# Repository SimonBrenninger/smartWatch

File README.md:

# smartWatch

is a simple, digital wristwatch that uses LEDs to indicate the position of each clock arm.

## Smart Features

The smartWatch incorporates an nRF52810 for handling BLE connectivity to send the monitored data regularly to the host device.

## PCB Design

The PCB was designed using [KiCad](https://kicad.org).

PCB front-side

PCB back-side

## Future Features

A future revision will include a biomedical sensor to enable even more smart functionalities i.e. SpO2 and heart-rate measurements.

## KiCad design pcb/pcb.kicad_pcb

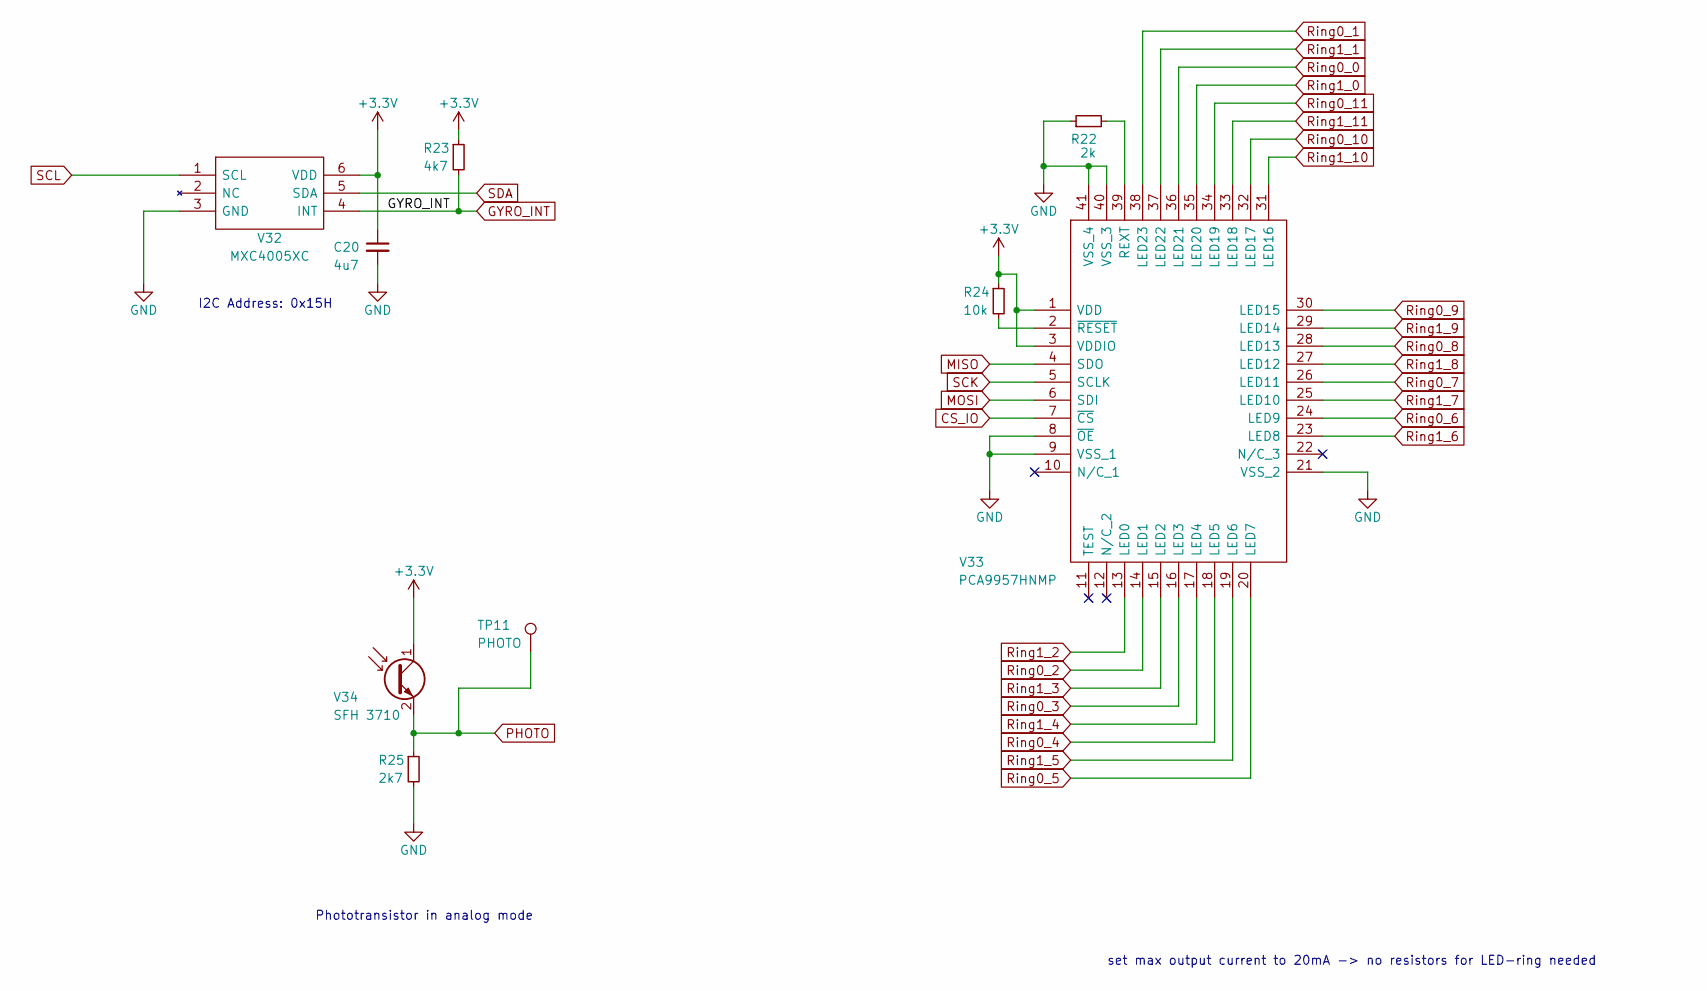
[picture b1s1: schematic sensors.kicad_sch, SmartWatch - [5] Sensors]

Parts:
C20: 4u7; C_0603_1608Metric
R22: 2k; R_0603_1608Metric
R23: 4k7; R_0603_1608Metric
R24: 10k; R_0603_1608Metric
R25: 2k7; R_0603_1608Metric
TP11: PHOTO; TestPoint_Pad_D1.0mm
V32: MXC4005XC; Mouser Part Number 438-MXC4005XC
V33: PCA9957HNMP; QFN-40-1EP_5x5mm_P0.4mm_EP3.6x3.6mm; Manufacturer_Part_Number PCA9957HNMP; Mouser Part Number PCA9957HNMP
V34: SFH 3710; LEDC2012X95N; Mouser Part Number SFH 3710-Z

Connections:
3.3V: C20.1, R23.1, R24.1, V32.6 (VDD), V33.1 (VDD), V33.3 (VDDIO), V34.1 (C); also elsewhere on the board
BAT_PROT-: C20.2, R22.1, R25.2, V32.3 (GND), V33.8 (~OE), V33.9 (VSS_1), V33.21 (VSS_2), V33.40 (VSS_3), V33.41 (VSS_4); also elsewhere on the board
CS_IO: V33.7 (~CS); also elsewhere on the board
GYRO_INT: R23.2, V32.4 (INT); also elsewhere on the board
MISO: V33.4 (SDO); also elsewhere on the board
MOSI: V33.6 (SDI); also elsewhere on the board
unnamed: R22.2, V33.39 (REXT)
unnamed: R24.2, V33.2 (~RESET)
PHOTO: R25.1, TP11.1, V34.2 (E); also elsewhere on the board
Ring0_0: V33.36 (LED21); also elsewhere on the board
Ring0_1: V33.38 (LED23); also elsewhere on the board
Ring0_2: V33.14 (LED1); also elsewhere on the board
Ring0_3: V33.16 (LED3); also elsewhere on the board
Ring0_4: V33.18 (LED5); also elsewhere on the board
Ring0_5: V33.20 (LED7); also elsewhere on the board
Ring0_6: V33.24 (LED9); also elsewhere on the board
Ring0_7: V33.26 (LED11); also elsewhere on the board
Ring0_8: V33.28 (LED13); also elsewhere on the board
Ring0_9: V33.30 (LED15); also elsewhere on the board
Ring0_10: V33.32 (LED17); also elsewhere on the board
Ring0_11: V33.34 (LED19); also elsewhere on the board
Ring1_0: V33.35 (LED20); also elsewhere on the board
Ring1_1: V33.37 (LED22); also elsewhere on the board
Ring1_2: V33.13 (LED0); also elsewhere on the board
Ring1_3: V33.15 (LED2); also elsewhere on the board
Ring1_4: V33.17 (LED4); also elsewhere on the board
Ring1_5: V33.19 (LED6); also elsewhere on the board
Ring1_6: V33.23 (LED8); also elsewhere on the board
Ring1_7: V33.25 (LED10); also elsewhere on the board
Ring1_8: V33.27 (LED12); also elsewhere on the board
Ring1_9: V33.29 (LED14); also elsewhere on the board
Ring1_10: V33.31 (LED16); also elsewhere on the board
Ring1_11: V33.33 (LED18); also elsewhere on the board
SCK: V33.5 (SCLK); also elsewhere on the board
SCL: V32.1 (SCL); also elsewhere on the board
SDA: V32.5 (SDA); also elsewhere on the board

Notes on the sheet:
set max output current to 20mA -> no resistors for LED-ring needed
I2C Address: 0x15H
Phototransistor in analog mode

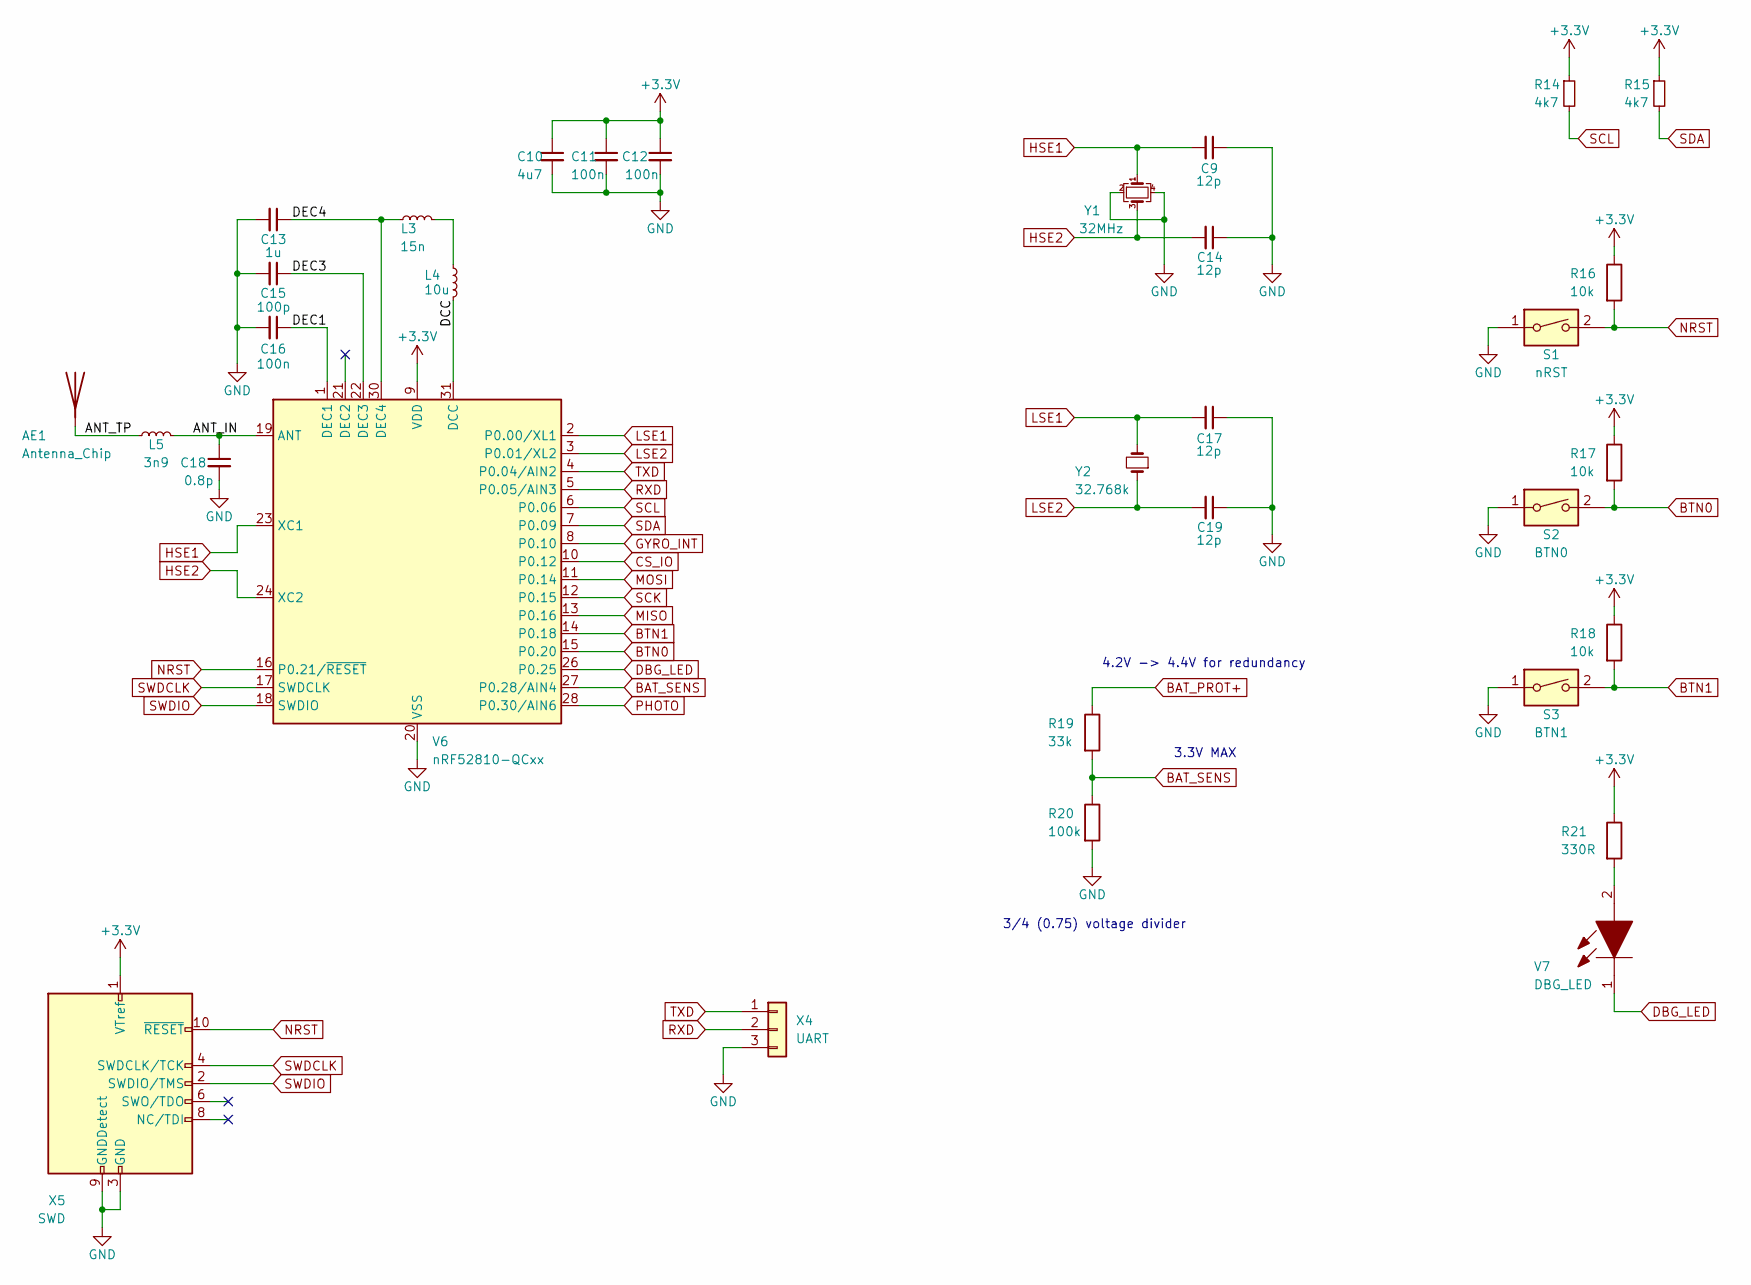
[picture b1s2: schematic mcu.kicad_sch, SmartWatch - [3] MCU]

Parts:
AE1: Antenna_Chip; Ignion_NN01-102_BT_WIFI
C9, C14, C17, C19: 12p; C_0603_1608Metric
C10: 4u7; C_0603_1608Metric
C11, C12, C16: 100n; C_0603_1608Metric
C13: 1u; C_0603_1608Metric
C15: 100p; C_0603_1608Metric
C18: 0.8p; C_0603_1608Metric
L3: 15n; L_0603_1608Metric
L4: 10u; L_0603_1608Metric
L5: 3n9; L_0603_1608Metric
R14, R15: 4k7; R_0603_1608Metric
R16, R17, R18: 10k; R_0603_1608Metric
R19: 33k; R_0603_1608Metric
R20: 100k; R_0603_1608Metric
R21: 330R; R_0603_1608Metric
S1: nRST; SW_SPST_EVQP2
S2: BTN0; Tactile_Panasonic_EVQP7J01P
S3: BTN1; Tactile_Panasonic_EVQP7J01P
V6: nRF52810-QCxx; QFN-32-1EP_5x5mm_P0.5mm_EP3.6x3.6mm
V7: DBG_LED; LEDC1608X80N; Mouser Part Number 710-150060SS75000
X4: UART; PinHeader_2x03_P1.27mm_Vertical_SMD
X5: SWD; PinHeader_2x05_P1.27mm_Vertical_SMD
Y1: 32MHz; Crystal_SMD_2520-4Pin_2.5x2.0mm; Mouser Part Number ECS-320-8-36CKM-TR3
Y2: 32.768k; Crystal_SMD_3215-2Pin_3.2x1.5mm; Mouser Part Number ECS-.327-9-34B-C-TR

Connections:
3.3V: C10.1, C11.1, C12.1, R14.1, R15.1, R16.1, R17.1, R18.1, R21.1, V6.9 (VDD), V6.25 (VDD), V6.32 (VDD), X5.1 (VTref); also elsewhere on the board
/MCU/ANT_IN: C18.1, L5.2, V6.19 (ANT)
/MCU/ANT_TP: AE1.1 (A), L5.1
/MCU/DCC: L4.1, V6.31 (DCC)
/MCU/DEC1: C16.1, V6.1 (DEC1)
/MCU/DEC3: C15.1, V6.22 (DEC3)
/MCU/DEC4: C13.1, L3.2, V6.30 (DEC4)
BAT_PROT+: R19.1; also elsewhere on the board
BAT_PROT-: C9.1, C10.2, C11.2, C12.2, C13.2, C14.1, C15.2, C16.2, C17.1, C18.2, C19.1, R20.2, S1.1, S2.1, S3.1, V6.20 (VSS), V6.29 (VSS), V6.33 (VSS), X4.3, X5.3 (GND), X5.5 (GND), X5.9 (GNDDetect), Y1.2, Y1.4; also elsewhere on the board
BAT_SENS: R19.2, R20.1, V6.27 (P0.28/AIN4)
BTN0: R17.2, S2.2, V6.15 (P0.20)
BTN1: R18.2, S3.2, V6.14 (P0.18)
CS_IO: V6.10 (P0.12); also elsewhere on the board
DBG_LED: V6.26 (P0.25), V7.1
GYRO_INT: V6.8 (P0.10); also elsewhere on the board
HSE1: C9.2, V6.23 (XC1), Y1.1
HSE2: C14.2, V6.24 (XC2), Y1.3
LSE1: C17.2, V6.2 (P0.00/XL1), Y2.2
LSE2: C19.2, V6.3 (P0.01/XL2), Y2.1
MISO: V6.13 (P0.16); also elsewhere on the board
MOSI: V6.11 (P0.14); also elsewhere on the board
NRST: R16.2, S1.2, V6.16 (P0.21/~RESET), X5.10 (~RESET)
unnamed: L3.1, L4.2
unnamed: R21.2, V7.2
PHOTO: V6.28 (P0.30/AIN6); also elsewhere on the board
RXD: V6.5 (P0.05/AIN3), X4.2
SCK: V6.12 (P0.15); also elsewhere on the board
SCL: R14.2, V6.6 (P0.06); also elsewhere on the board
SDA: R15.2, V6.7 (P0.09); also elsewhere on the board
SWDCLK: V6.17 (SWDCLK), X5.4 (SWDCLK/TCK)
SWDIO: V6.18 (SWDIO), X5.2 (SWDIO/TMS)
TXD: V6.4 (P0.04/AIN2), X4.1

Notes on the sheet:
4.2V -> 4.4V for redundancy
3/4 (0.75) voltage divider
3.3V MAX

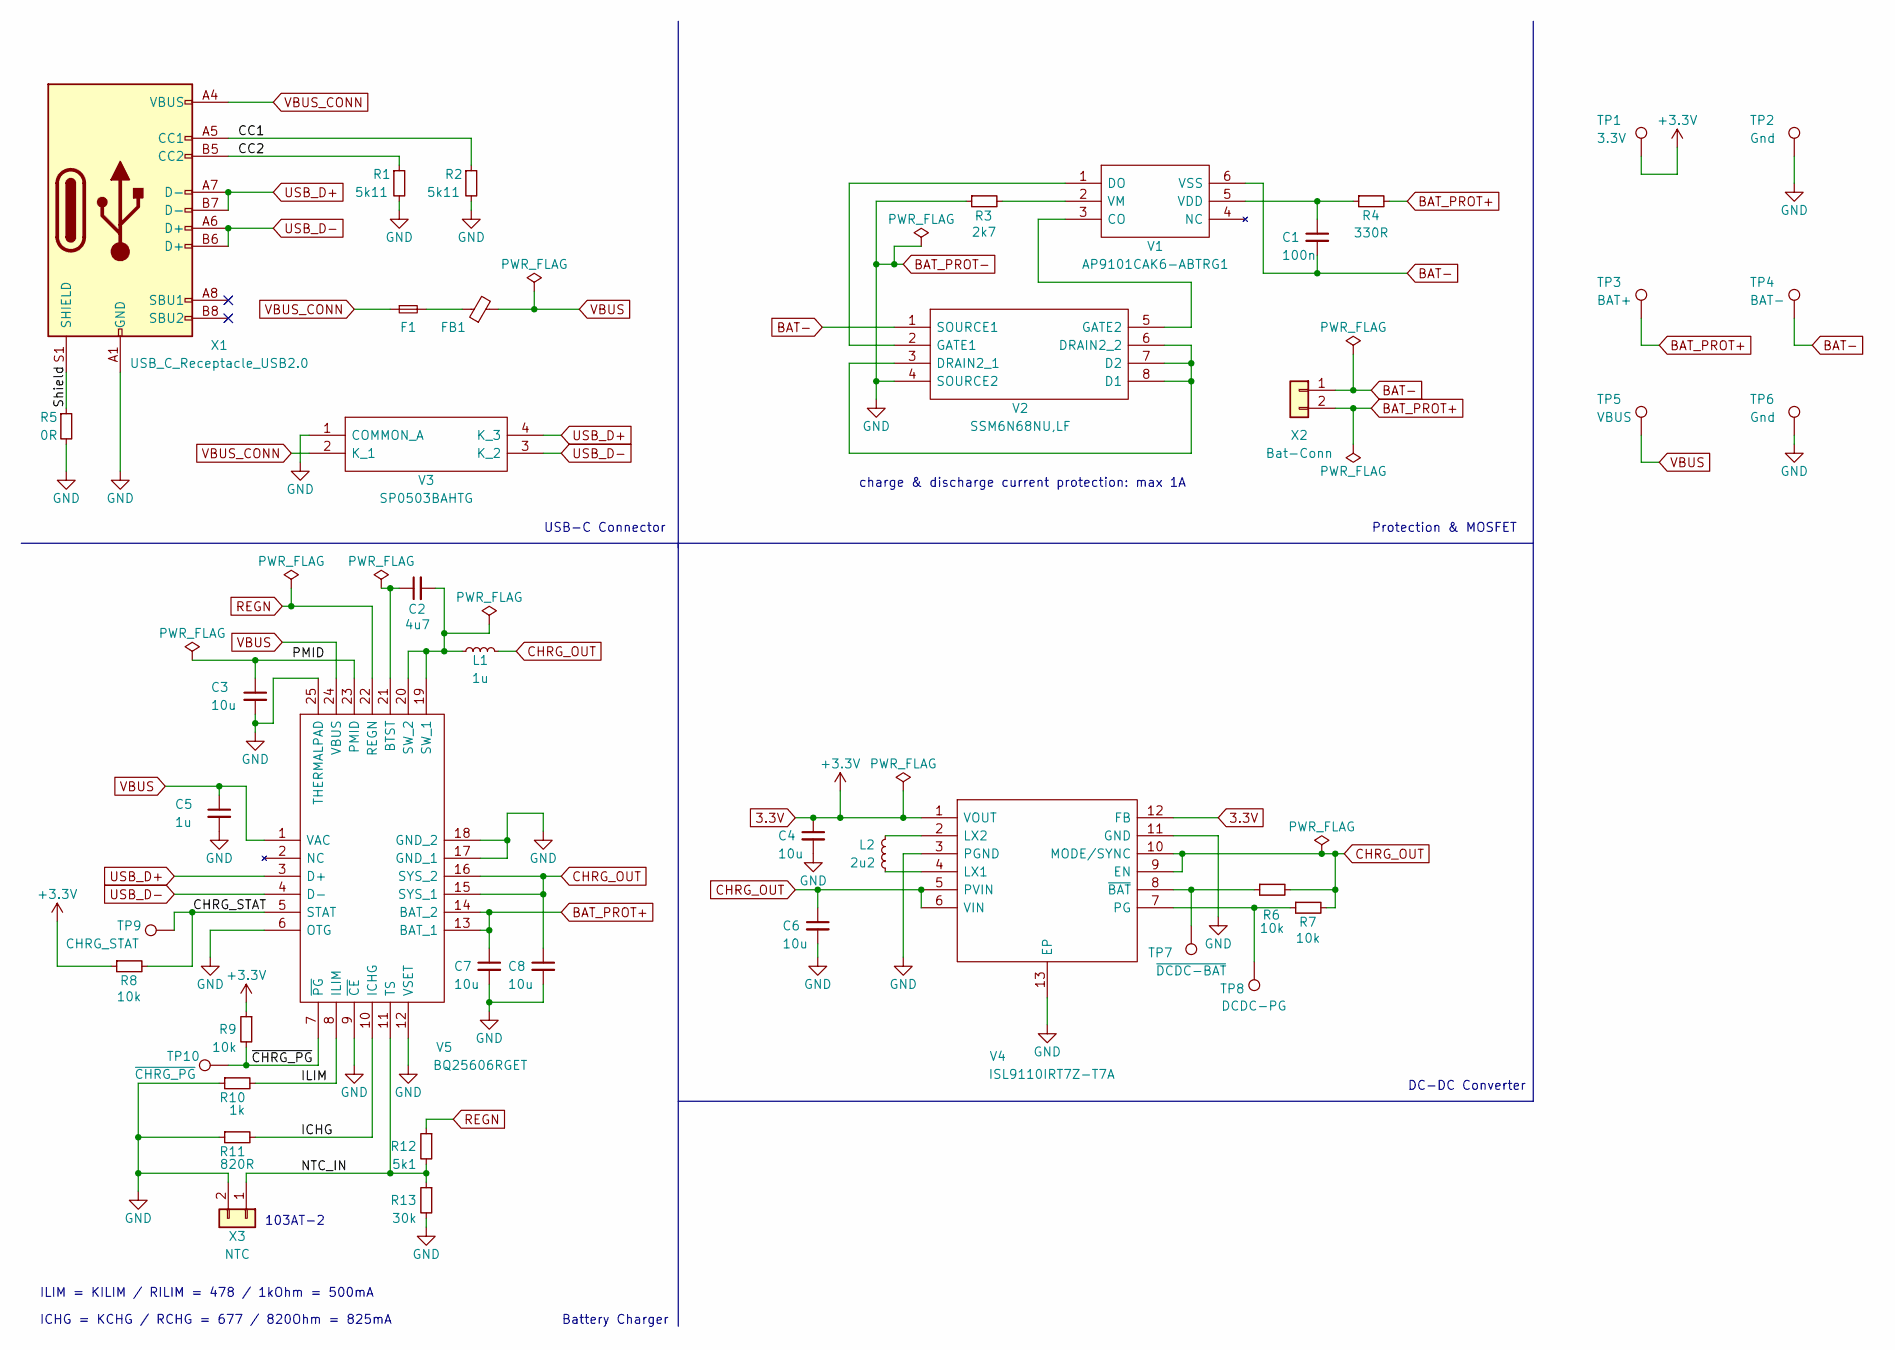
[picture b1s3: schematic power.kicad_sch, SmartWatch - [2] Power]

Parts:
C1: 100n; C_0603_1608Metric
C2: 4u7; C_0603_1608Metric
C3, C4, C6, C7, C8: 10u; C_0603_1608Metric
C5: 1u; C_0603_1608Metric
F1: Fuse_1A; Fuse_0603_1608Metric_Pad1.05x0.95mm_HandSolder
FB1: FerriteBead_Small; L_0805_2012Metric
L1: 1u; L_0603_1608Metric
L2: 2u2; L_1008_2520Metric
R1, R2: 5k11; R_0603_1608Metric
R3: 2k7; R_0603_1608Metric
R4: 330R; R_2512_6332Metric
R5: 0R; R_0603_1608Metric
R6, R7, R8, R9: 10k; R_0603_1608Metric
R10: 1k; R_0603_1608Metric
R11: 820R; R_0603_1608Metric
R12: 5k1; R_0603_1608Metric
R13: 30k; R_0603_1608Metric
TP1: 3.3V; TestPoint_Pad_D1.0mm
TP2, TP6: Gnd; TestPoint_Pad_D1.0mm
TP3: BAT+; TestPoint_Pad_D1.0mm
TP4: BAT-; TestPoint_Pad_D1.0mm
TP5: VBUS; TestPoint_Pad_D1.0mm
TP7: ~{DCDC-BAT}; TestPoint_Pad_D1.0mm
TP8: DCDC-PG; TestPoint_Pad_D1.0mm
TP9: CHRG_STAT; TestPoint_Pad_D1.0mm
TP10: ~{CHRG_PG}; TestPoint_Pad_D1.0mm
V1: AP9101CAK6-ABTRG1; SOT95P285X140-6N; Mouser Part Number 621-AP9101CAK6ABTRG1
V2: SSM6N68NU,LF; SSM6N68NULF; Manufacturer_Part_Number SSM6N68NU,LF; Mouser Part Number 757-SSM6N68NULF
V3: SP0503BAHTG; Manufacturer_Part_Number SP0503BAHTG; Mouser Part Number 576-SP0503BAHTG
V4: ISL9110IRT7Z-T7A; SON40P300X300X75-13N; Mouser Part Number 968-ISL9110IRT7Z-T7A
V5: BQ25606RGET; QFN50P400X400X100-25N; Mouser2 Part Number 595-BQ25606RGET
X1: USB_C_Receptacle_USB2.0; USB_C_Receptacle_Amphenol_12401598; Mouser Part Number 12401598E4#2A
X2: Bat-Conn; JST_PH_B2B-PH-SM4-TB_1x02-1MP_P2.00mm_Vertical
X3: NTC; PinHeader_P2mm_1x02_SMD

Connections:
3.3V: C4.1, R8.1, R9.1, TP1.1, V4.1 (VOUT), V4.12 (FB); also elsewhere on the board
/Power/CC1: R2.1, X1.A5 (CC1)
/Power/CC2: R1.1, X1.B5 (CC2)
/Power/CHRG_STAT: R8.2, TP9.1, V5.5 (STAT)
/Power/ICHG: R11.2, V5.10 (ICHG)
/Power/ILIM: R10.2, V5.8 (ILIM)
/Power/NTC_IN: R12.2, R13.1, V5.11 (TS), X3.1
/Power/PMID: C3.1, V5.23 (PMID)
/Power/Shield: R5.1, X1.S1 (SHIELD)
/Power/~CHRG_PG: R9.2, TP10.1, V5.7 (~PG)
BAT-: C1.2, TP4.1, V1.6 (VSS), V2.1 (SOURCE1), X2.1
BAT_PROT+: C7.1, R4.2, TP3.1, V5.13 (BAT_1), V5.14 (BAT_2), X2.2; also elsewhere on the board
BAT_PROT-: C3.2, C4.2, C5.2, C6.2, C7.2, C8.2, R1.2, R2.2, R3.1, R5.2, R10.1, R11.1, R13.2, TP2.1, TP6.1, V2.4 (SOURCE2), V3.1 (COMMON_A), V4.3 (PGND), V4.11 (GND), V4.13 (EP), V5.6 (OTG), V5.9 (~CE), V5.12 (VSET), V5.17 (GND_1), V5.18 (GND_2), V5.25 (THERMALPAD), X1.A1 (GND), X1.A12 (GND), X1.B1 (GND), X1.B12 (GND), X3.2; also elsewhere on the board
CHRG_OUT: C6.1, C8.1, L1.2, R6.2, R7.2, V4.5 (PVIN), V4.6 (VIN), V4.9 (EN), V4.10 (MODE/SYNC), V5.15 (SYS_1), V5.16 (SYS_2)
unnamed: C1.1, R4.1, V1.5 (VDD)
unnamed: C2.1, V5.21 (BTST)
unnamed: C2.2, L1.1, V5.19 (SW_1), V5.20 (SW_2)
unnamed: F1.2, FB1.1
unnamed: L2.1, V4.2 (LX2)
unnamed: L2.2, V4.4 (LX1)
unnamed: R3.2, V1.2 (VM)
unnamed: R6.1, TP7.1, V4.8 (~BAT)
unnamed: R7.1, TP8.1, V4.7 (PG)
unnamed: V1.1 (DO), V2.2 (GATE1)
unnamed: V1.3 (CO), V2.5 (GATE2)
unnamed: V2.3 (DRAIN2_1), V2.6 (DRAIN2_2), V2.7 (D2), V2.8 (D1)
REGN: R12.1, V5.22 (REGN)
USB_D+: V3.4 (K_3), V5.3 (D+), X1.A7 (D-), X1.B7 (D-)
USB_D-: V3.3 (K_2), V5.4 (D-), X1.A6 (D+), X1.B6 (D+)
VBUS: C5.1, FB1.2, TP5.1, V5.1 (VAC), V5.24 (VBUS)
VBUS_CONN: F1.1, V3.2 (K_1), X1.A4 (VBUS), X1.A9 (VBUS), X1.B4 (VBUS), X1.B9 (VBUS)

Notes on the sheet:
ICHG = KCHG / RCHG = 677 / 820Ohm = 825mA
ILIM = KILIM / RILIM = 478 / 1kOhm = 500mA
DC-DC Converter
USB-C Connector
charge & discharge current protection: max 1A
Protection & MOSFET
103AT-2
Battery Charger

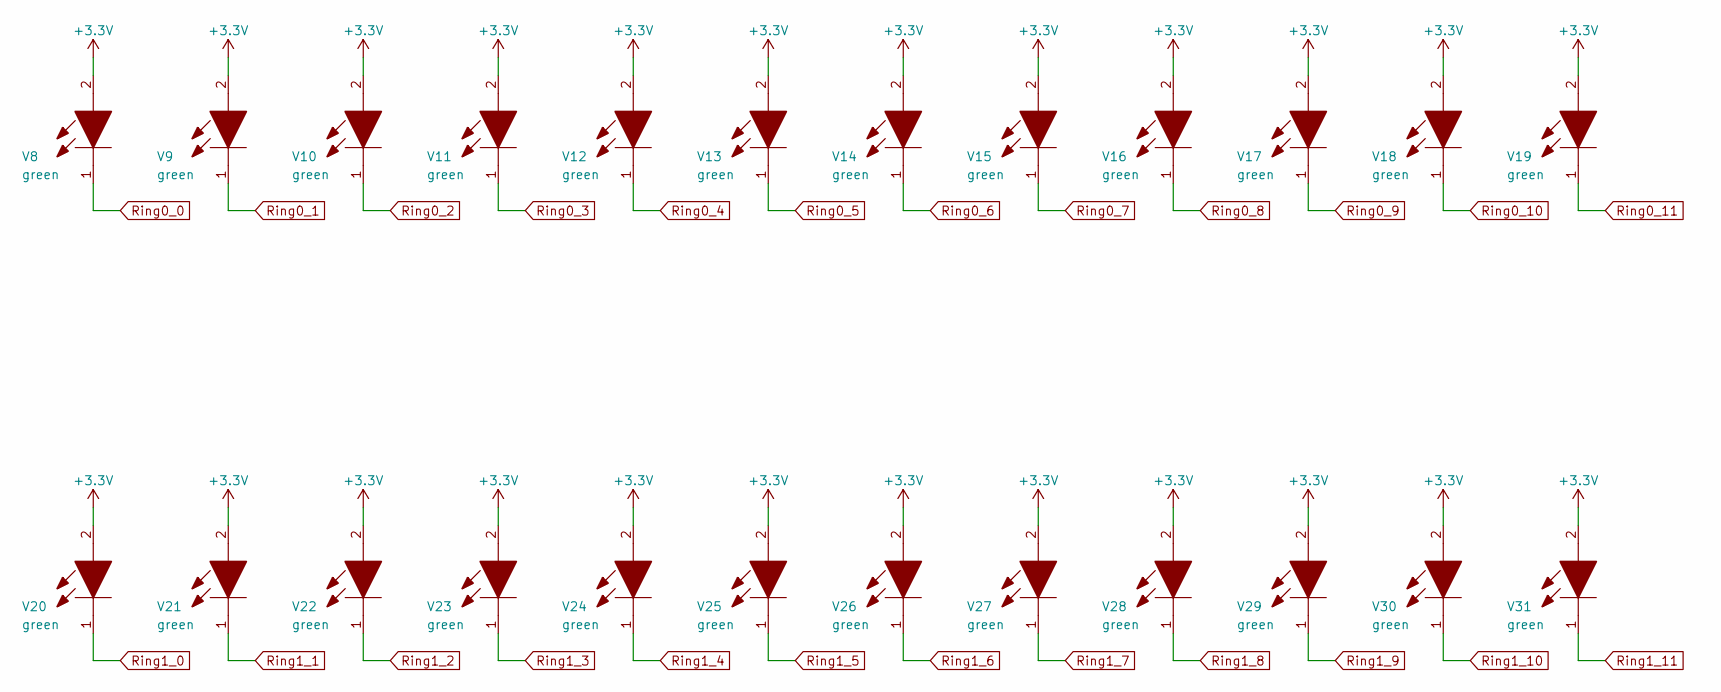
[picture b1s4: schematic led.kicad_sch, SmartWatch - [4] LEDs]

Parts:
V8, V9, V10, V11, V12, V13, V14, V15, V16, V17, V18, V19, V20, V21, V22, V23, V24, V25, V26, V27, V28, V29, V30, V31: green; LEDM2012X80N; Mouser Part Number 710-150080GS75000

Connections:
3.3V: V8.2, V9.2, V10.2, V11.2, V12.2, V13.2, V14.2, V15.2, V16.2, V17.2, V18.2, V19.2, V20.2, V21.2, V22.2, V23.2, V24.2, V25.2, V26.2, V27.2, V28.2, V29.2, V30.2, V31.2; also elsewhere on the board
Ring0_0: V8.1; also elsewhere on the board
Ring0_1: V9.1; also elsewhere on the board
Ring0_2: V10.1; also elsewhere on the board
Ring0_3: V11.1; also elsewhere on the board
Ring0_4: V12.1; also elsewhere on the board
Ring0_5: V13.1; also elsewhere on the board
Ring0_6: V14.1; also elsewhere on the board
Ring0_7: V15.1; also elsewhere on the board
Ring0_8: V16.1; also elsewhere on the board
Ring0_9: V17.1; also elsewhere on the board
Ring0_10: V18.1; also elsewhere on the board
Ring0_11: V19.1; also elsewhere on the board
Ring1_0: V20.1; also elsewhere on the board
Ring1_1: V21.1; also elsewhere on the board
Ring1_2: V22.1; also elsewhere on the board
Ring1_3: V23.1; also elsewhere on the board
Ring1_4: V24.1; also elsewhere on the board
Ring1_5: V25.1; also elsewhere on the board
Ring1_6: V26.1; also elsewhere on the board
Ring1_7: V27.1; also elsewhere on the board
Ring1_8: V28.1; also elsewhere on the board
Ring1_9: V29.1; also elsewhere on the board
Ring1_10: V30.1; also elsewhere on the board
Ring1_11: V31.1; also elsewhere on the board

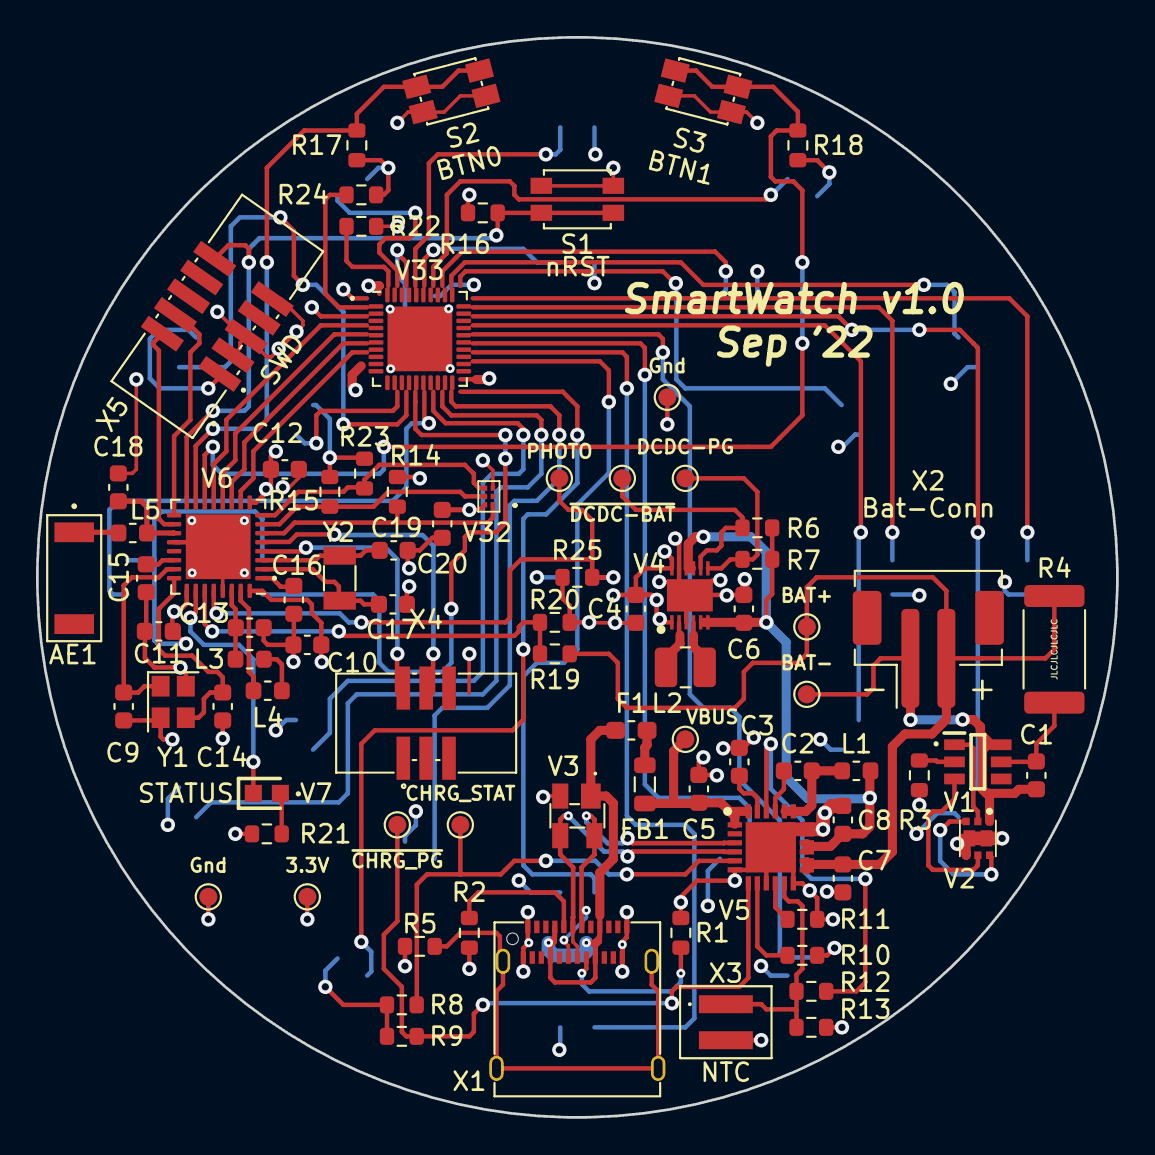
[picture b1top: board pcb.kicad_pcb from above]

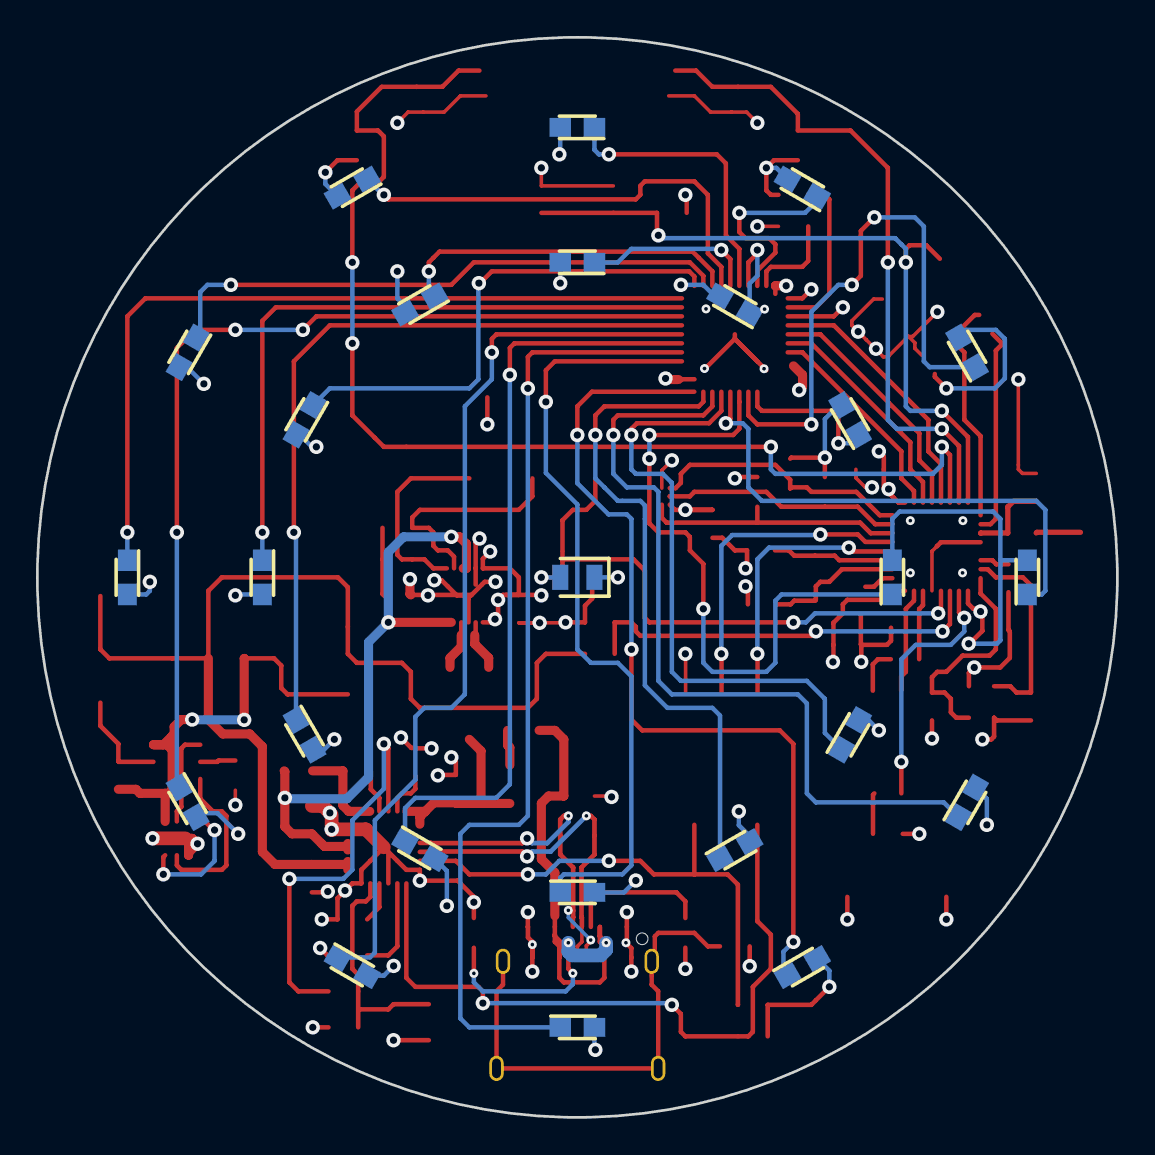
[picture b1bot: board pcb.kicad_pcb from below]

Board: 4 copper layers, 60.0 x 60.0 mm, 108 parts (25 on the bottom side), 86 nets.

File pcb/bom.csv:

Item,Qty,Reference(s),Value,Mouser Part Number,,Total Qty
1,1,AE1,Antenna_Chip,NN01-102,,3
2,4,"C1, C12, C13, C14",100n,963-EMK107B7104KAHT,,12
3,3,"C2, C11, C19",4u7,81-GRM188Z71C475KE1J,,9
4,5,"C3, C4, C5, C6, C7",10u,81-GRM188Z71A106KA3D,,15
5,1,C8,1u,187-CL10B105KO8NNND,,3
6,1,C9,100p,603-CC603JRNPO8BN101,,3
7,4,"C10, C15, C16, C18",12p,603-CC603GRNPO9BN120,,12
8,1,C17,0.8p,791-0603N0R8C500CT,,3
9,1,L1,1u,810-TFM160808ALC1R0A,,3
10,1,L2,2u2,739-MGV2520102R2M-10,,3
11,1,L3,15n,609-L-14C15NKV4T,,3
12,1,L4,10u,810-MLZ1608M100WT000,,3
13,1,L5,3.9n,81-LQW18AS3N9J00D,,3
14,2,"R1, R2",5k11,603-RC0603FR-105K11L,,6
15,2,"R3, R25",2k7,71-CRCW06032K70FKEAH,,6
16,1,R4,330R,71-CRCW0603330RFKEAH,,3
17,1,R5,0R,,,3
18,5,"R6, R7, R8, R9, R24",10k,667-ERJ-3GEYJ103V,,15
19,1,R10,1k,603-AF0603JR-071KL,,3
20,1,R11,820R,603-AC0603JR-07820RL,,3
21,1,R12,5k1,660-RK73B1JTTDD512J,,3
22,1,R13,30k,755-ESR03EZPJ303,,3
23,3,"R14, R15, R23",4k7,660-RK73B1JTTD472J,,9
24,3,"R16, R17, R18",10k,667-ERJ-3GEYJ103V,,9
25,1,R19,33k,603-RC0603JR-0733KL,,3
26,1,R20,100k,667-ERJ-3EKF1003V,,3
27,1,R21,330R,755-SDR03EZPJ331,,3
28,1,R22,2k,791-WR06X2001FTL,,3
29,1,S1,nRST,612-TL3780AF240QG,,3
30,1,S2,BTN0,667-EVQP7J01P,,3
31,1,S3,BTN1,667-EVQP7J01P,,3
44,1,V1,AP9101CAK6-ABTRG1,621-AP9101CAK6ABTRG1,,3
45,1,V2,"SSM6N68NU,LF",757-SSM6N68NULF,,3
46,1,V3,SP0503BAHTG,576-SP0503BAHTG,,3
47,1,V4,ISL9110IRT7Z-T7A,968-ISL9110IRT7Z-T7A,,3
48,1,V5,BQ25606RGET,BQ25606RGET,,3
49,1,V6,nRF52810-QFxx,949-NRF52810-QCAA-T,,3
50,1,V7,DBG_LED,710-150060SS75000,,3
51,24,"V8, V9, V10, V11, V12, V13, V14, V15, V16, V17, V18, V19, V20, V21, V22, V23, V24, V25, V26, V27, V28, V29, V30, V31",green,710-150080GS75000,,48
52,1,V32,MXC4005XC,438-MXC4005XC,,3
53,1,V33,PCA9957HNMP,PCA9957HNMP,,2
54,1,V34,SFH 3710,SFH 3710-Z,,3
55,1,X1,USB_C_Receptacle_USB2.0,12401598E4#2A,,3
56,1,X2,Bat-Conn,,,3
57,1,X3,NTC-Conn,,,3
58,1,X4,SWD-Conn,,,3
59,1,X5,UART_Conn,,,3
60,1,Y1,32MHz,ECS-320-8-36CKM-TR3,,3
61,1,Y2,32.768k,ECS-.327-9-34B-C-TR,,3

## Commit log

2022-09-04 add pcb cad project
2022-09-04 finish mcu connections
2022-09-04 changed MCU package
2022-09-04 finish overview schematic page
2022-09-04 generate bom; select C's & L's
2022-09-04 add LEDs for LED ring
2022-09-04 add charging & preotection circuit
2022-09-04 add testpoints & connectors
2022-09-04 add usb-c footprint
2022-09-04 add dc-dc converter, add sensors
2022-09-04 add back layer led-ring
2022-09-04 finish mcu section in pcb layout
2022-09-04 add pcb layout
2022-09-04 add power section on pcb layout
2022-09-04 finish back layer placement
2022-09-04 route mcu section
2022-09-06 add 3d models for pcb layout
2022-09-06 generate gerber files
2022-11-23 add features for v2 in pcb/todo
2022-11-23 add hvqfn adapter pcb
2022-11-23 add protection circuit measurements
2022-11-23 add zephyr board description
2022-11-23 edit README.md
2022-11-25 add pcb fixes
2023-02-19 finish QFN adapter layout
2023-02-19 add test application
2023-02-19 change UART & SWD conn
2023-02-19 add led driver docs
2023-02-25 add datasheets
2023-02-25 add accel test
2023-03-04 add LICENSE
2023-04-21 add mxc400 bit definitions
2023-04-21 edit gitignore
2023-05-04 edit devicetree, change docs
2023-05-04 Revert "edit gitignore"
    This reverts commit 7d0c4b0df1450372f941e83b064acac36d25e600.
2023-05-04 edit README
2023-05-18 add pca9957 wrapper
2023-05-18 add docs
2023-07-09 add rtc; re-organize dir
2023-07-17 add ipc
2023-07-17 change openocd configs
2023-07-19 add mxc400 isr
2023-10-12 add pca thread queue
2023-10-12 add source lib layer
2023-12-26 edit conf
2024-01-29 rename firmware directory
2025-02-16 remove kicad backup files
